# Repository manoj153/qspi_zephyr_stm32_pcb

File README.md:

### Author: Manojkumar <manoj@electrolance.com>
# PCB designed to test and integrate QSPI Flash, nucleo-h723zg, and Zephyr

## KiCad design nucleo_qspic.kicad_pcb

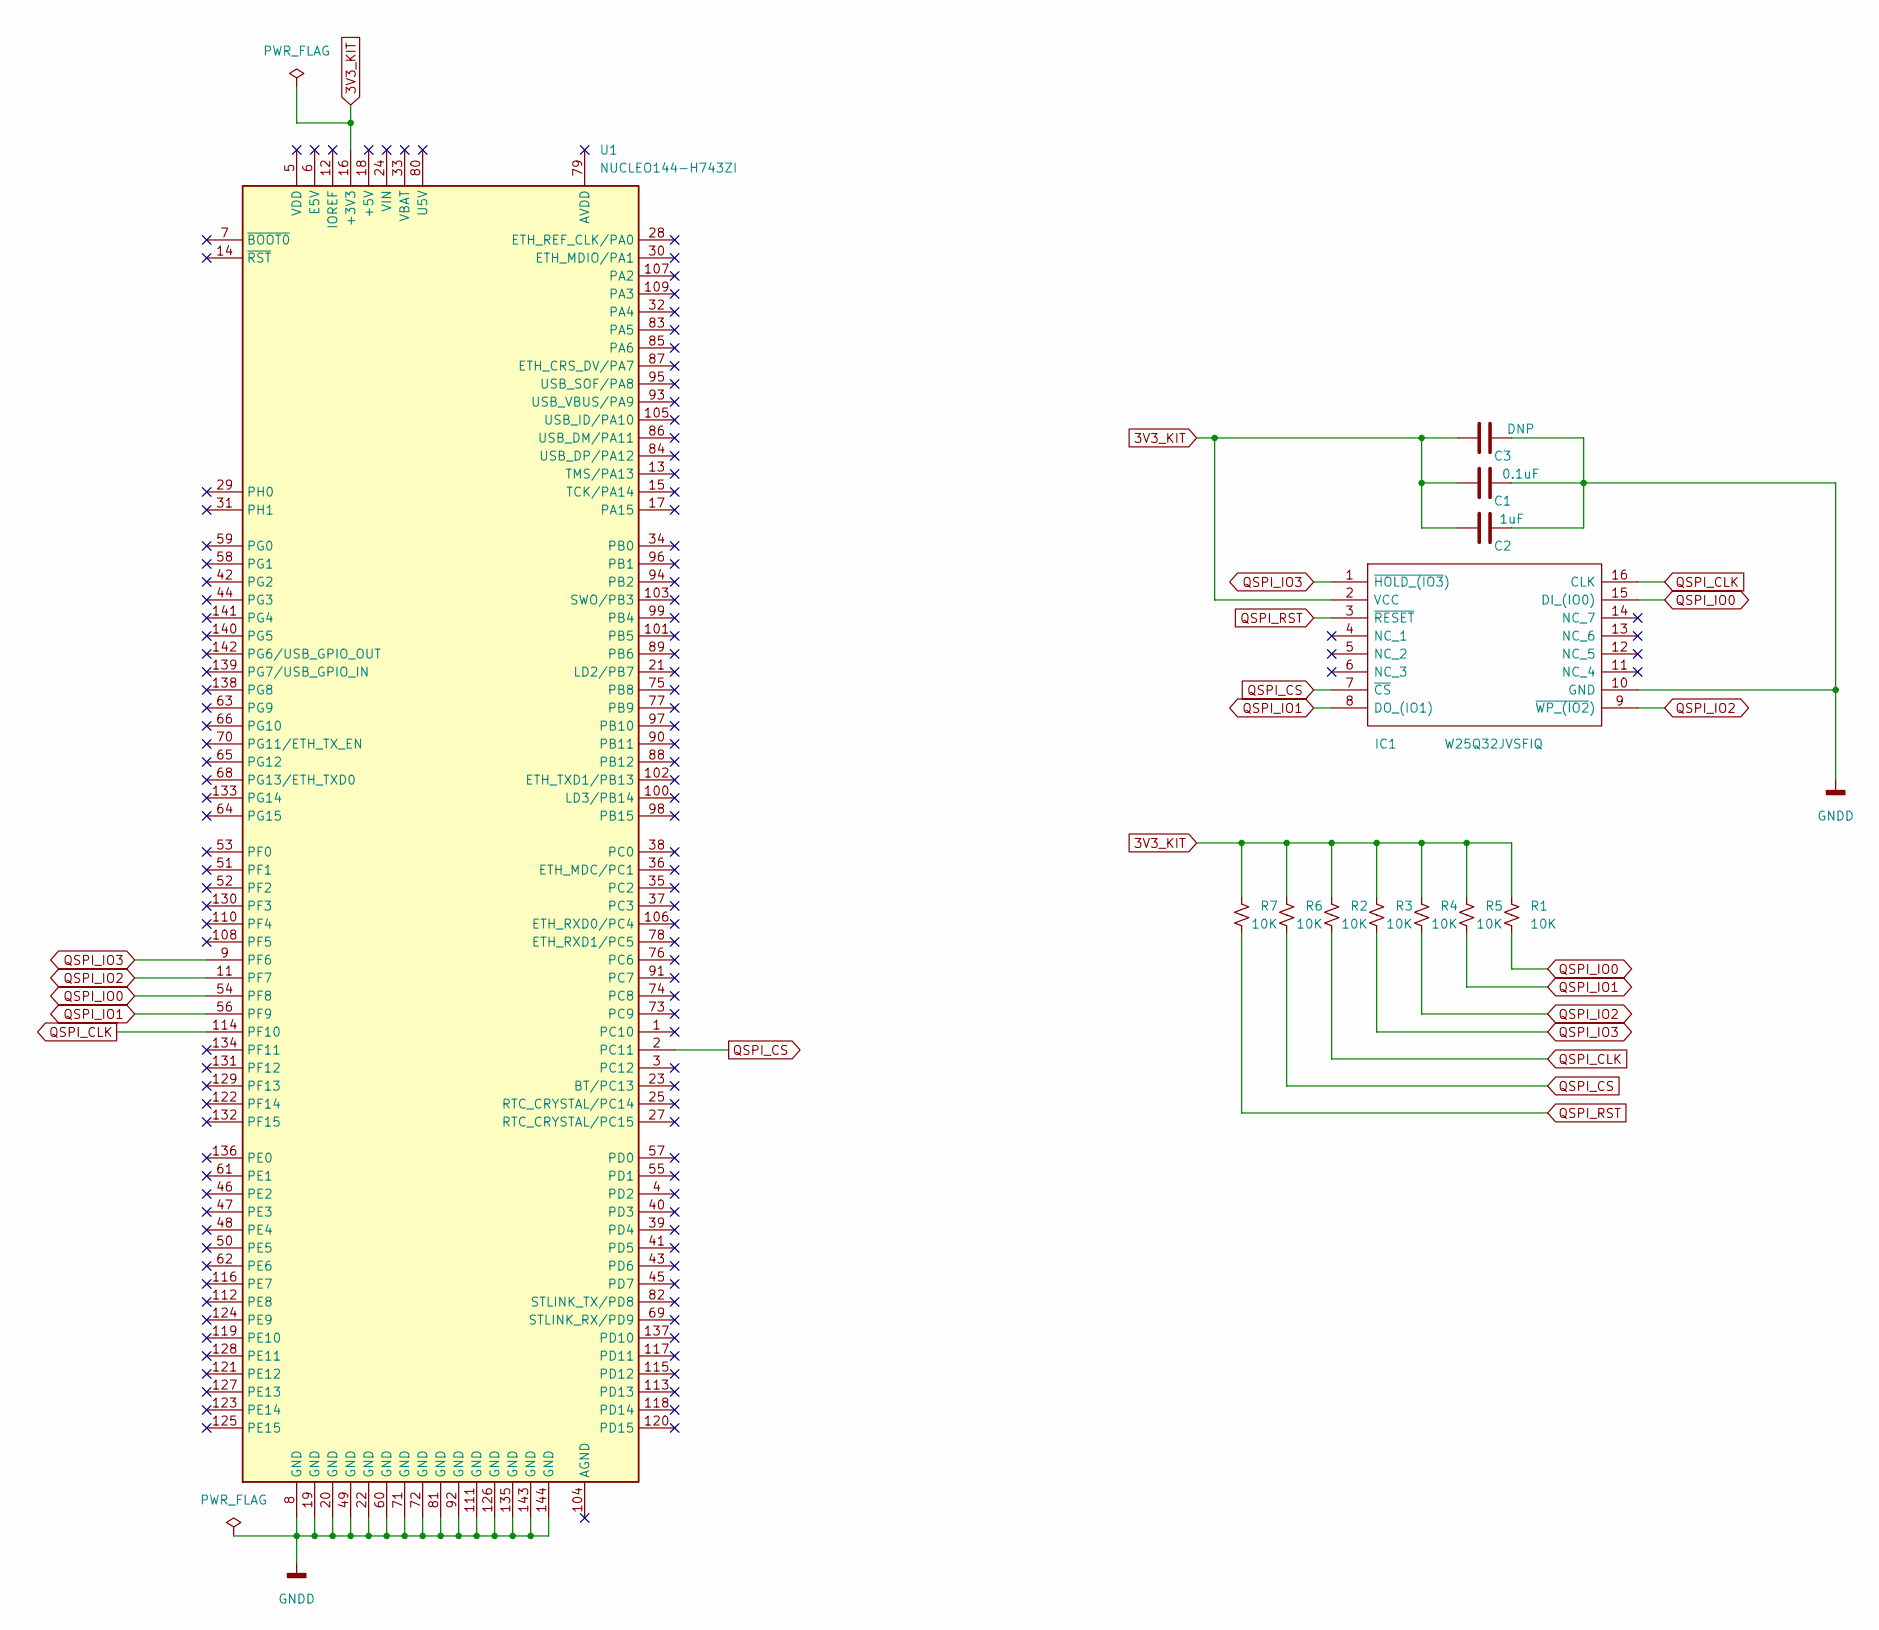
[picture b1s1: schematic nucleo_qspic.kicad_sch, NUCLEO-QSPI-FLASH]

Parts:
C1: 0.1uF; C_0805_2012Metric
C2: 1uF; C_0805_2012Metric
C3: DNP; C_0805_2012Metric
IC1: W25Q32JVSFIQ; SOIC127P1032X264-16N; Manufacturer_Part_Number W25Q32JVSFIQ; Mouser Part Number 454-W25Q32JVSFIQ
R1, R2, R3, R4, R5, R6, R7: 10K; R_0805_2012Metric
U1: NUCLEO144-H743ZI; ST_Morpho_Connector_144_STLink_MountingHoles

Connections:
3V3_KIT: C1.2, C2.2, C3.2, IC1.2 (VCC), R1.1, R2.1, R3.1, R4.1, R5.1, R6.1, R7.1, U1.16 (+3V3)
GNDD: C1.1, C2.1, C3.1, IC1.10 (GND), U1.8 (GND), U1.19 (GND), U1.20 (GND), U1.22 (GND), U1.49 (GND), U1.60 (GND), U1.71 (GND), U1.72 (GND), U1.81 (GND), U1.92 (GND), U1.111 (GND), U1.126 (GND), U1.135 (GND), U1.143 (GND), U1.144 (GND)
QSPI_CLK: IC1.16 (CLK), R2.2, U1.114 (PF10)
QSPI_CS: IC1.7 (~CS), R6.2, U1.2 (PC11)
QSPI_IO0: IC1.15 (DI_(IO0)), R1.2, U1.54 (PF8)
QSPI_IO1: IC1.8 (DO_(IO1)), R5.2, U1.56 (PF9)
QSPI_IO2: IC1.9 (~WP_(IO2)), R4.2, U1.11 (PF7)
QSPI_IO3: IC1.1 (~HOLD_(IO3)), R3.2, U1.9 (PF6)
QSPI_RST: IC1.3 (~RESET), R7.2

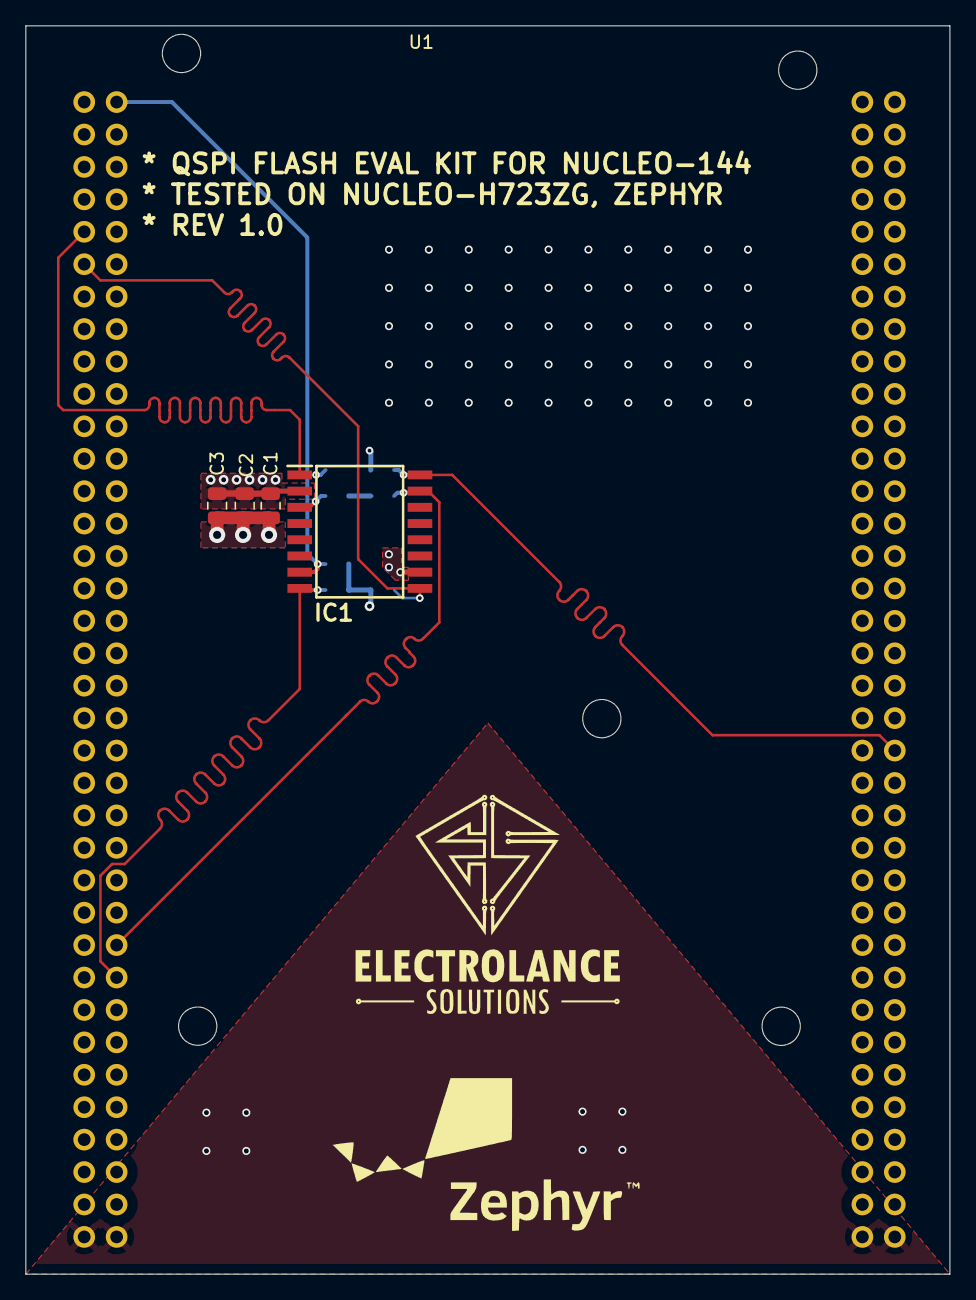
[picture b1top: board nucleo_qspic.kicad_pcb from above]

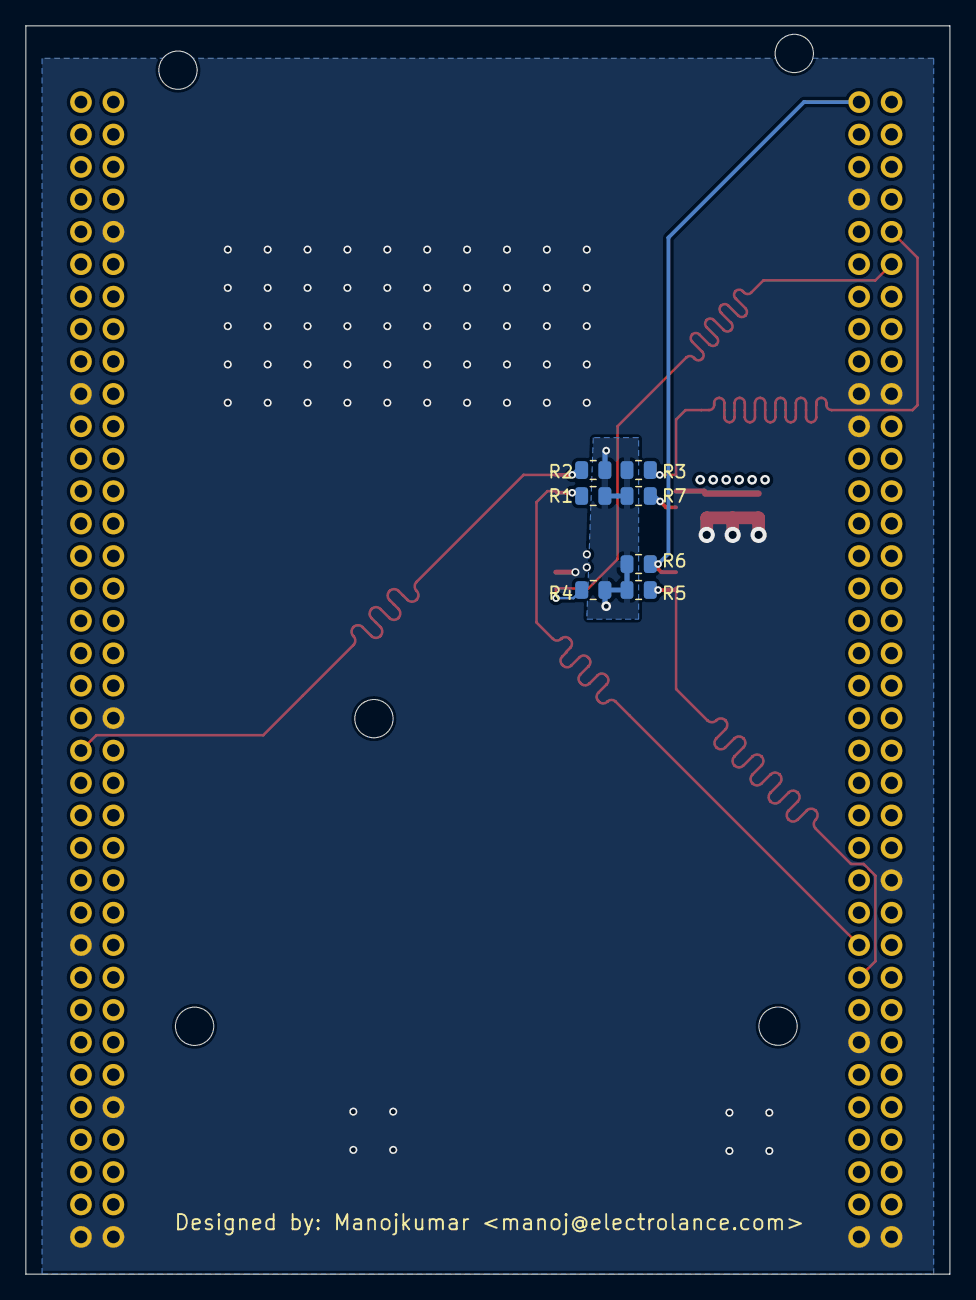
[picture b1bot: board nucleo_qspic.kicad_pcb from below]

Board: 4 copper layers, 72.4 x 97.8 mm, 12 parts (7 on the bottom side), 9 nets.

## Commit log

2022-05-24 make clk line width same with other qspi signal, give pull up value to 10K(optional) and change capacitance value to what is available in inventory
2022-05-24 add schematic image to README
